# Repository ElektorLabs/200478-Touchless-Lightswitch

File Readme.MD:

# 200478 - Touchless Lightswitch

## WARNING

This is work in progress and not finished. There may be leathal bugs inside the design. Use at your own risk

## Not working yet
```
- Webpage not included
- Size to large
- Mains supply not safe
```
## Description

This is the prototype of a touchless opperating lightswitch using the MGC3130 from Micorchip and an ESP32 as MCU
Code is done in PlatformIO and dependencys should be loaded automatically. 

A PCB done in KiCad and an Enclosure done in FreeCAD are also included. 

## Firmware installation

```bash
Download the code and import it into PlatformIO
```

## Contributing
Pull requests are welcome. For major changes, please open an issue first to discuss what you would like to change.

## Branches
Be aware that this project may use different branches and check out the one you like to use

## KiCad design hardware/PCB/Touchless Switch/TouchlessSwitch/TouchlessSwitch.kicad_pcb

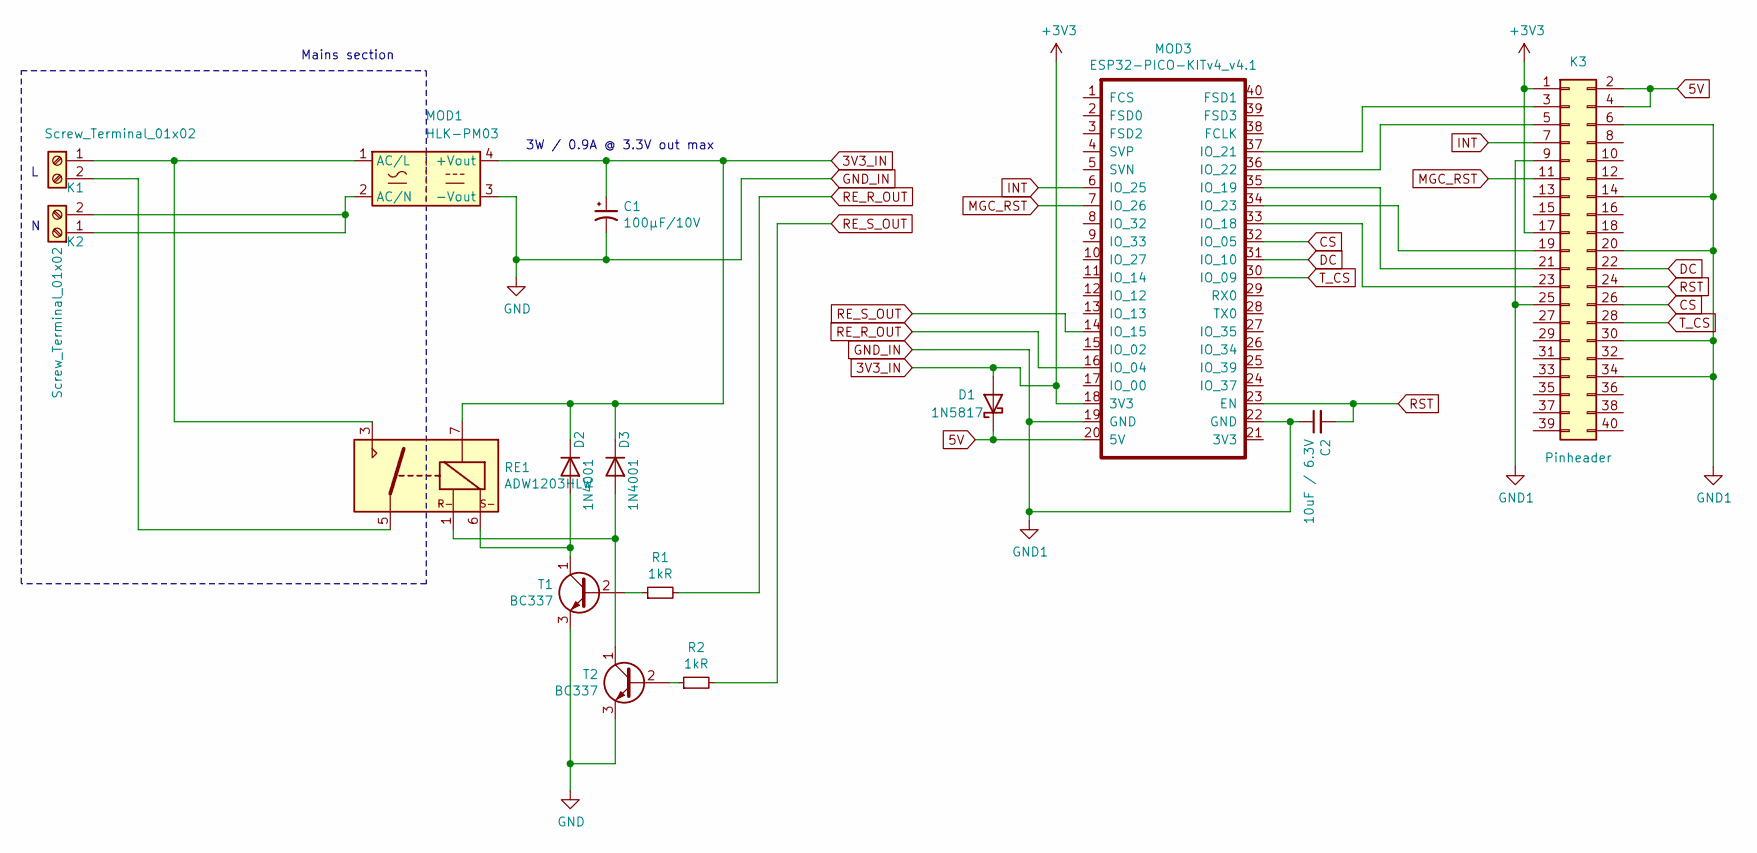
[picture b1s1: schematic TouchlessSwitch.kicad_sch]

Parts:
C1: 100µF/10V; CP_Radial_D5.0mm_P2.00mm
C2: 10uF / 6.3V; CP_Radial_D5.0mm_P2.00mm
D1: 1N5817; D_DO-41_SOD81_P7.62mm_Horizontal
D2, D3: 1N4001; D_DO-41_SOD81_P7.62mm_Horizontal
K1, K2: Screw_Terminal_01x02; TerminalBlock_Altech_AK300-2_P5.00mm
K3: Pinheader; PinHeader_2x20_P2.54mm_Vertical
MOD1: HLK-PM03; Converter_ACDC_HiLink_HLK-PMxx
MOD3: ESP32-PICO-KITv4_v4.1; DIP-40_W17.78mm_Socket
R1, R2: 1kR; R_Axial_DIN0207_L6.3mm_D2.5mm_P10.16mm_Horizontal
RE1: ADW1203HLW; Relay_1P1T_NO_10x24x18.8mm_Panasonic_ADW11xxxxW_THT
T1, T2: BC337; TO-92_Inline

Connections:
3V3_IN: C1.1, D1.2 (A), D2.1 (K), D3.1 (K), K3.1, K3.17, MOD1.4 (+Vout), MOD3.18 (3V3), RE1.7
5V: D1.1 (K), K3.2, K3.4, MOD3.20 (5V)
CS: K3.26, MOD3.32 (IO_05)
DC: K3.22, MOD3.31 (IO_10)
GND_IN: C1.2, C2.1, K3.6, K3.9, K3.14, K3.20, K3.25, K3.30, K3.34, MOD1.3 (-Vout), MOD3.19 (GND), MOD3.22 (GND), T1.3 (E), T2.3 (E)
INT: K3.7, MOD3.6 (IO_25)
MGC_RST: K3.11, MOD3.7 (IO_26)
unnamed: D2.2 (A), RE1.6, T1.1 (C)
unnamed: D3.2 (A), RE1.1, T2.1 (C)
unnamed: K1.1, MOD1.1 (AC/L), RE1.3
unnamed: K1.2, RE1.5
unnamed: K2.1, K2.2, MOD1.2 (AC/N)
unnamed: K3.3, MOD3.37 (IO_21)
unnamed: K3.5, MOD3.36 (IO_22)
unnamed: K3.19, MOD3.34 (IO_23)
unnamed: K3.21, MOD3.35 (IO_19)
unnamed: K3.23, MOD3.33 (IO_18)
unnamed: R1.1, T1.2 (B)
unnamed: R2.1, T2.2 (B)
RE_R_OUT: MOD3.16 (IO_04), R1.2
RE_S_OUT: MOD3.14 (IO_15), R2.2
RST: C2.2, K3.24, MOD3.23 (EN)
T_CS: K3.28, MOD3.30 (IO_09)

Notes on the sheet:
Mains section
3W / 0.9A @ 3.3V out max

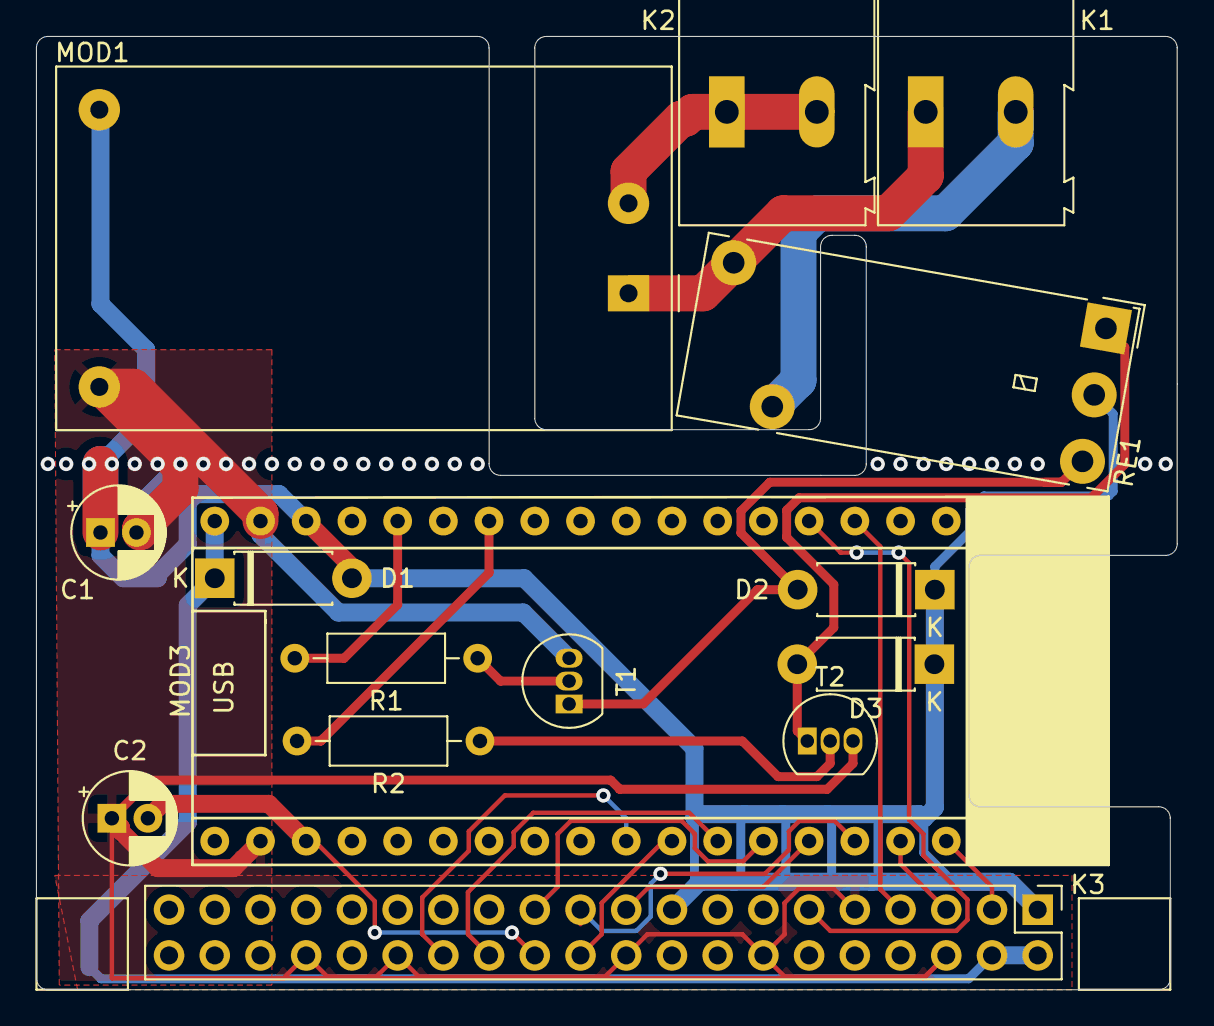
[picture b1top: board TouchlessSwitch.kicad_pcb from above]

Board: 2 copper layers, 63.4 x 53.0 mm, 15 parts (0 on the bottom side), 23 nets.

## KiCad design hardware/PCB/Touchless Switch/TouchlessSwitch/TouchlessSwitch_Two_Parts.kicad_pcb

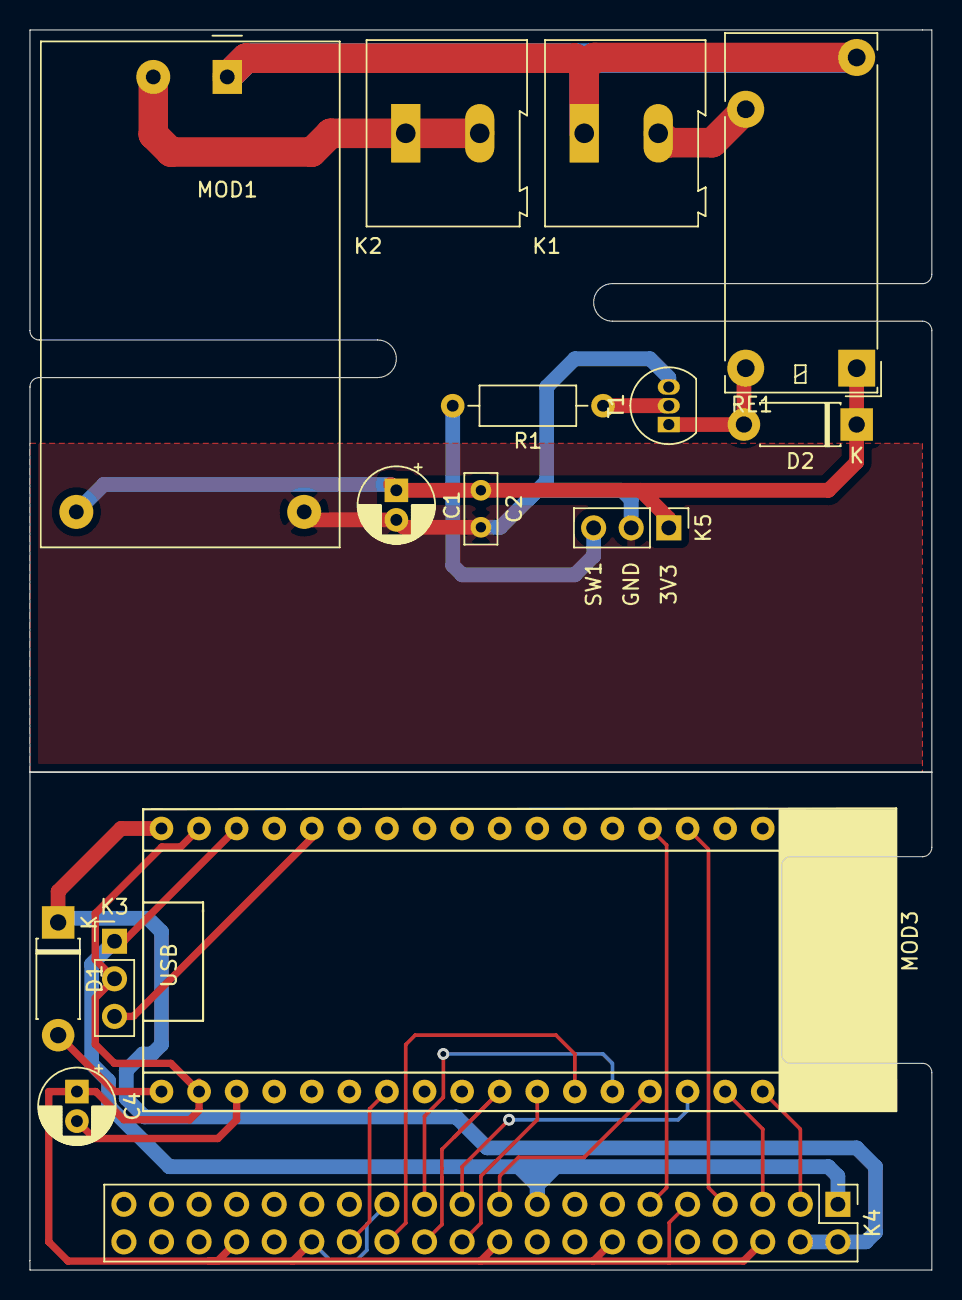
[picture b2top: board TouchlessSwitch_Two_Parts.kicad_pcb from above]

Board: 2 copper layers, 61.0 x 83.8 mm, 15 parts (0 on the bottom side), 25 nets.

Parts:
C1: 100µF / 6.3V; CP_Radial_D5.0mm_P2.00mm
C2: 100nF / 6.3V; C_Rect_L4.6mm_W2.0mm_P2.50mm_MKS02_FKP02
C4: 10uF / 6.3V; CP_Radial_D5.0mm_P2.00mm
D1, D2: D; D_DO-41_SOD81_P7.62mm_Horizontal
K1, K2: Screw_Terminal_01x02; TerminalBlock_Altech_AK300-2_P5.00mm
K3, K5: Conn_01x03; PinHeader_1x03_P2.54mm_Vertical
K4: Conn_02x20_Odd_Even; PinHeader_2x20_P2.54mm_Vertical
MOD1: HLK-PM03; Converter_ACDC_HiLink_HLK-PMxx
MOD3: ESP32-PICO-KITv4_v4.1; DIP-40_W17.78mm_Socket
R1: 1kR; R_Axial_DIN0207_L6.3mm_D2.5mm_P10.16mm_Horizontal
RE1: ADW11; Relay_1P1T_NO_10x24x18.8mm_Panasonic_ADW11xxxxW_THT
T1: BC337; TO-92_Inline

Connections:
5V: D1.1, K4.2, K4.4, MOD3.20
+3V3: K3.1, K4.1, K4.17, MOD3.18
CS: K4.26, MOD3.32
DC: K4.22, MOD3.31
GND: C1.2, C2.2, K5.2, MOD1.3, T1.3
GND1: C4.1, K3.2, K4.6, K4.9, K4.14, K4.20, K4.25, K4.30, K4.34, MOD3.19, MOD3.22
INT: K4.7, MOD3.6
MGC_RST: K4.11, MOD3.7
unnamed: C1.1, C2.1, D2.1, K5.1, MOD1.4, RE1.1
unnamed: C4.2, MOD3.23
unnamed: D1.2, MOD3.21
unnamed: D2.2, RE1.6, T1.1
unnamed: K1.1, MOD1.1, RE1.3
unnamed: K1.2, RE1.5
unnamed: K2.1, K2.2, MOD1.2
unnamed: K3.3, MOD3.16
unnamed: K4.3, MOD3.37
unnamed: K4.5, MOD3.36
unnamed: K4.19, MOD3.34
unnamed: K4.21, MOD3.35
unnamed: K4.23, MOD3.33
unnamed: K5.3, R1.2
unnamed: R1.1, T1.2
RST: K4.24, MOD3.30
T_CS: K4.28, MOD3.27

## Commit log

2021-10-26 Update for latching relay
2021-10-26 PCB Files Update for latching relay
